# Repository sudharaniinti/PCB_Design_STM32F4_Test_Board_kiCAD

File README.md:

# STM32F4_based_PCB_Design_using_kiCAD
This repository contains all the files related to the design of a PCB using KICAD. The PCB is based on the STM32F4-based microcontroller and incorporates a USB interface and a Buck converter.

This repository includes the following files:

1. **Schematic (PDF File)**: A detailed PDF file that presents the circuit connections and component arrangement in a clear and concise manner.

2. **Schematic (kiCAD File)**: The original KICAD file of the schematic, allowing for easy editing and customization.

3. **Netlist**: The netlist file, an essential component of the design, which provides information about the electrical connections between various components and ensures accurate signal flow within the PCB.

4. **PCB Design**: The PCB layout file displaying the placement of components, routing traces, and layers used.

5. **Bill of Materials(BOM)**: The BOM file (in CSV format) listing all the components used in the design along with their quantities and specifications.

6. **Gerber Files**: These files (in ZIP format) are necessary for PCB fabrication. They include all the data required by the manufacturer to produce the physical PCB, such as copper layers, solder mask, silkscreen, drill holes, and board outline.

7. **Component Placement File**: This file (in CSV format) provides the precise coordinates and orientations for placing components on the PCB. It assists during the assembly process by ensuring accurate component placement.

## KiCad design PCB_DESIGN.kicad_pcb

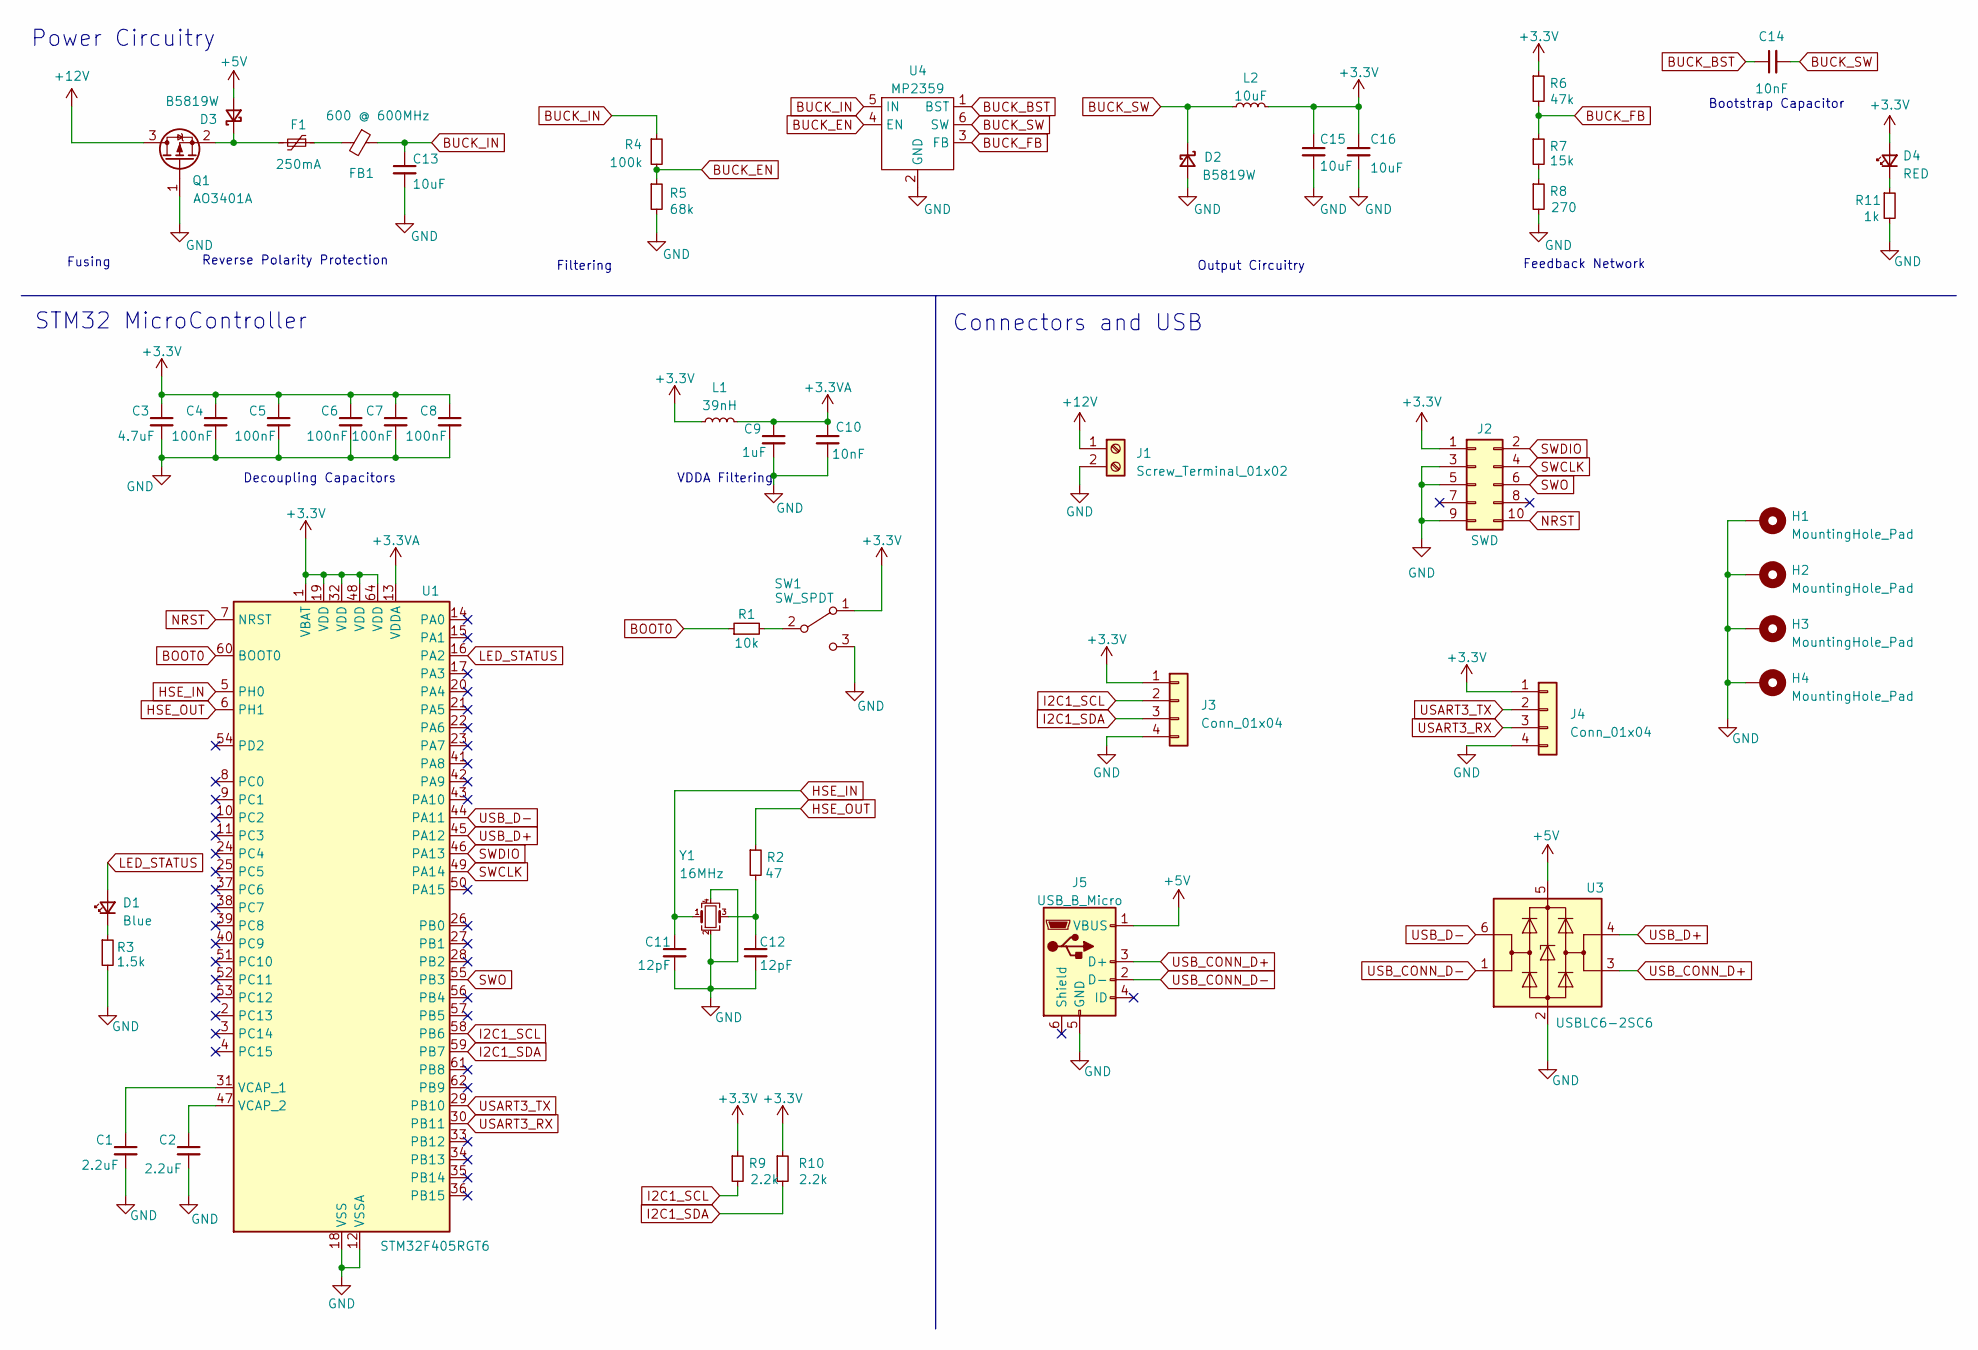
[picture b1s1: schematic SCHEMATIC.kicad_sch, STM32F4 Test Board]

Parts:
C1, C2: 2.2uF; C_0603_1608Metric
C3: 4.7uF; C_0603_1608Metric
C4, C5, C6, C7, C8: 100nF; C_0402_1005Metric
C9: 1uF; C_0402_1005Metric
C10: 10nF; C_0402_1005Metric
C11, C12: 12pF; C_0402_1005Metric
C13, C15, C16: 10uF; C_1206_3216Metric
C14: 10nF; C_0603_1608Metric
D1: Blue; LED_0603_1608Metric
D2, D3: B5819W; D_SOD-123
D4: RED; LED_0603_1608Metric
F1: 250mA; Fuse_1206_3216Metric
FB1: 600 @ 600MHz; L_0805_2012Metric
H1, H2, H3, H4: MountingHole_Pad; MountingHole_4.3mm_M4_Pad_Via
J1: Screw_Terminal_01x02; TerminalBlock_Phoenix_PT-1,5-2-3.5-H_1x02_P3.50mm_Horizontal
J2: SWD; PinHeader_2x05_P1.27mm_Vertical_SMD
J3, J4: Conn_01x04; Molex_PicoBlade_53048-0410_1x04_P1.25mm_Horizontal
J5: USB_B_Micro; USB_Micro-B_GCT_USB3076-30-A
L1: 39nH; L_0402_1005Metric
L2: 10uF; L_Sunlord_MWSA0518S
Q1: AO3401A; SOT-23
R1: 10k; R_0402_1005Metric
R2: 47; R_0402_1005Metric
R3: 1.5k; R_0603_1608Metric
R4: 100k; R_0603_1608Metric
R5: 68k; R_0603_1608Metric
R6: 47k; R_0603_1608Metric
R7: 15k; R_0603_1608Metric
R8: 270; R_0603_1608Metric
R9, R10: 2.2k; R_0402_1005Metric
R11: 1k; R_0603_1608Metric
SW1: SW_SPDT; SW_SPDT_PCM12
U1: STM32F405RGT6; LQFP-64_10x10mm_P0.5mm
U3: USBLC6-2SC6; SOT-23-6
U4: MP2359; SOT-23-6
Y1: 16MHz; Crystal_SMD_3225-4Pin_3.2x2.5mm

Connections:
+3.3V: C3.1, C4.1, C5.1, C6.1, C7.1, C8.1, C15.1, C16.1, D4.2 (A), J2.1, J3.1, J4.1, L1.1, L2.2, R6.1, R9.1, R10.1, SW1.1 (A), U1.1 (VBAT), U1.19 (VDD), U1.32 (VDD), U1.48 (VDD), U1.64 (VDD)
+3.3VA: C9.1, C10.1, L1.2, U1.13 (VDDA)
+5V: D3.2 (A), J5.1 (VBUS), U3.5 (VBUS)
+12V: J1.1, Q1.3 (D)
BOOT0: R1.1, U1.60 (BOOT0)
BUCK_BST: C14.1, U4.1 (BST)
BUCK_EN: R4.2, R5.1, U4.4 (EN)
BUCK_FB: R6.2, R7.1, U4.3 (FB)
BUCK_IN: C13.1, FB1.1, R4.1, U4.5 (IN)
BUCK_SW: C14.2, D2.1 (K), L2.1, U4.6 (SW)
GND: C1.2, C2.2, C3.2, C4.2, C5.2, C6.2, C7.2, C8.2, C9.2, C10.2, C11.2, C12.2, C13.2, C15.2, C16.2, D2.2 (A), H1.1, H2.1, H3.1, H4.1, J1.2, J2.3, J2.5, J2.9, J3.4, J4.4, J5.5 (GND), Q1.1 (G), R3.2, R5.2, R8.2, R11.2, SW1.3 (C), U1.12 (VSSA), U1.18 (VSS), U1.63 (VSS), U3.2 (GND), U4.2 (GND), Y1.2, Y1.4
HSE_IN: C11.1, U1.5 (PH0), Y1.1
HSE_OUT: R2.1, U1.6 (PH1)
I2C1_SCL: J3.2, R9.2, U1.58 (PB6)
I2C1_SDA: J3.3, R10.2, U1.59 (PB7)
LED_STATUS: D1.2 (A), U1.16 (PA2)
NRST: J2.10, U1.7 (NRST)
unnamed: C12.1, R2.2, Y1.3
unnamed: D1.1 (K), R3.1
unnamed: D3.1 (K), F1.2, Q1.2 (S)
unnamed: D4.1 (K), R11.1
unnamed: F1.1, FB1.2
unnamed: R7.2, R8.1
unnamed: R1.2, SW1.2 (B)
unnamed: C1.1, U1.31 (VCAP_1)
unnamed: C2.1, U1.47 (VCAP_2)
SWCLK: J2.4, U1.49 (PA14)
SWDIO: J2.2, U1.46 (PA13)
SWO: J2.6, U1.55 (PB3)
USART3_RX: J4.3, U1.30 (PB11)
USART3_TX: J4.2, U1.29 (PB10)
USB_CONN_D+: J5.3 (D+), U3.3 (I/O2)
USB_CONN_D-: J5.2 (D-), U3.1 (I/O1)
USB_D+: U1.45 (PA12), U3.4 (I/O2)
USB_D-: U1.44 (PA11), U3.6 (I/O1)

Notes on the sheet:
Decoupling Capacitors
Filtering
Fusing
Output Circuitry
Power Circuitry
VDDA Filtering
Feedback Network
Connectors and USB
STM32 MicroController
Reverse Polarity Protection
Bootstrap Capacitor

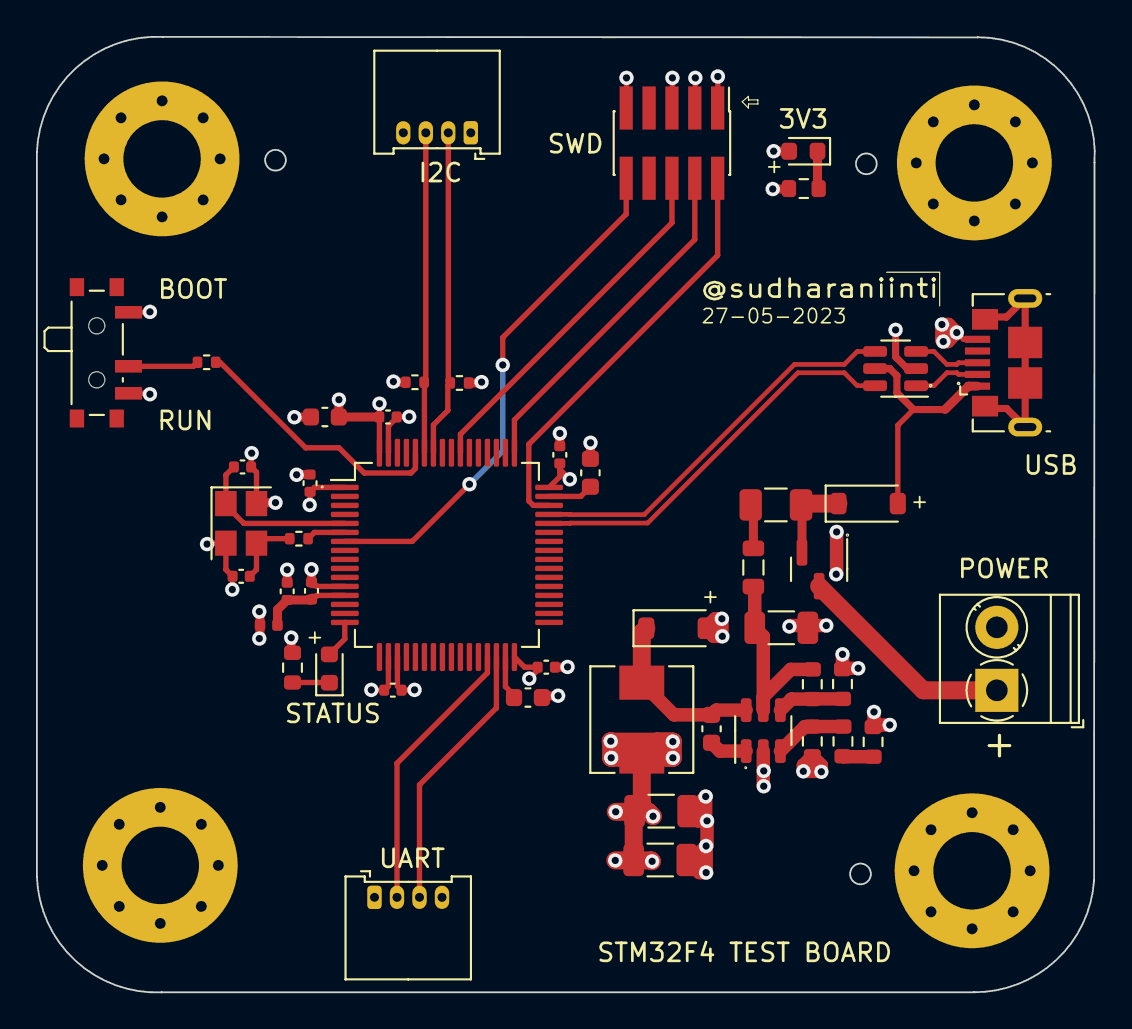
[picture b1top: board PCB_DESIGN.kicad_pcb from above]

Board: 4 copper layers, 58.8 x 53.1 mm, 50 parts (0 on the bottom side), 35 nets.

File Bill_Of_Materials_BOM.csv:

"Source:","E:\KiCAD_STM32\KiCAD_STM32.kicad_sch"
"Date:","5/28/2023 2:46:41 AM"
"Tool:","Eeschema 7.0.2"
"Generator:","C:\Program Files\KiCad\7.0\bin\scripting\plugins/bom_csv_grouped_by_value.py"
"Component Count:","50"

"Collated Components:"

"Item","Qty","Reference(s)","Value","LibPart","Footprint","Datasheet","DNP"
"1","2","C1, C2","2.2uF","Device:C_Small","Capacitor_SMD:C_0603_1608Metric","~",""
"2","1","C3","4.7uF","Device:C_Small","Capacitor_SMD:C_0603_1608Metric","~",""
"3","5","C4, C5, C6, C7, C8","100nF","Device:C_Small","Capacitor_SMD:C_0402_1005Metric","~",""
"4","1","C9","1uF","Device:C_Small","Capacitor_SMD:C_0402_1005Metric","~",""
"5","1","C10","10nF","Device:C_Small","Capacitor_SMD:C_0402_1005Metric","~",""
"6","2","C11, C12","12pF","Device:C_Small","Capacitor_SMD:C_0402_1005Metric","~",""
"7","3","C13, C15, C16","10uF","Device:C_Small","Capacitor_SMD:C_1206_3216Metric","~",""
"8","1","C14","10nF","Device:C_Small","Capacitor_SMD:C_0603_1608Metric","~",""
"9","1","D1","Blue","Device:LED_Small","LED_SMD:LED_0603_1608Metric","~",""
"10","2","D2, D3","B5819W","Device:D_Schottky_Small","Diode_SMD:D_SOD-123","~",""
"11","1","D4","RED","Device:LED_Small","LED_SMD:LED_0603_1608Metric","~",""
"12","1","F1","250mA","Device:Polyfuse_Small","Fuse:Fuse_1206_3216Metric","~",""
"13","1","FB1","600 @ 600MHz","Device:FerriteBead_Small","Inductor_SMD:L_0805_2012Metric","~",""
"14","4","H1, H2, H3, H4","MountingHole_Pad","Mechanical:MountingHole_Pad","MountingHole:MountingHole_4.3mm_M4_Pad_Via","~",""
"15","1","J1","Screw_Terminal_01x02","Connector:Screw_Terminal_01x02","TerminalBlock_Phoenix:TerminalBlock_Phoenix_PT-1,5-2-3.5-H_1x02_P3.50mm_Horizontal","~",""
"16","1","J2","SWD","Connector_Generic:Conn_02x05_Odd_Even","Connector_PinHeader_1.27mm:PinHeader_2x05_P1.27mm_Vertical_SMD","~",""
"17","2","J3, J4","Conn_01x04","Connector_Generic:Conn_01x04","Connector_Molex:Molex_PicoBlade_53048-0410_1x04_P1.25mm_Horizontal","~",""
"18","1","J5","USB_B_Micro","Connector:USB_B_Micro","Connector_USB:USB_Micro-B_GCT_USB3076-30-A","~",""
"19","1","L1","39nH","Device:L_Small","Inductor_SMD:L_0402_1005Metric","~",""
"20","1","L2","10uF","Device:L_Small","Inductor_SMD:L_Sunlord_MWSA0518S","~",""
"21","1","Q1","AO3401A","Transistor_FET:AO3401A","Package_TO_SOT_SMD:SOT-23","http://www.aosmd.com/pdfs/datasheet/AO3401A.pdf",""
"22","1","R1","10k","Device:R_Small","Resistor_SMD:R_0402_1005Metric","~",""
"23","1","R2","47","Device:R_Small","Resistor_SMD:R_0402_1005Metric","~",""
"24","1","R3","1.5k","Device:R_Small","Resistor_SMD:R_0603_1608Metric","~",""
"25","1","R4","100k","Device:R_Small","Resistor_SMD:R_0603_1608Metric","~",""
"26","1","R5","68k","Device:R_Small","Resistor_SMD:R_0603_1608Metric","~",""
"27","1","R6","47k","Device:R_Small","Resistor_SMD:R_0603_1608Metric","~",""
"28","1","R7","15k","Device:R_Small","Resistor_SMD:R_0603_1608Metric","~",""
"29","1","R8","270","Device:R_Small","Resistor_SMD:R_0603_1608Metric","~",""
"30","2","R9, R10","2.2k","Device:R_Small","Resistor_SMD:R_0402_1005Metric","~",""
"31","1","R11","1k","Device:R_Small","Resistor_SMD:R_0603_1608Metric","~",""
"32","1","SW1","SW_SPDT","Switch:SW_SPDT","Button_Switch_SMD:SW_SPDT_PCM12","~",""
"33","1","U1","STM32F405RGT6","MCU_ST_STM32F4:STM32F405RGTx","Package_QFP:LQFP-64_10x10mm_P0.5mm","https://www.st.com/resource/en/datasheet/stm32f405rg.pdf",""
"34","1","U3","USBLC6-2SC6","Power_Protection:USBLC6-2SC6","Package_TO_SOT_SMD:SOT-23-6","https://www.st.com/resource/en/datasheet/usblc6-2.pdf",""
"35","1","U4","MP2359",":MP2359_1","Package_TO_SOT_SMD:SOT-23-6","",""
"36","1","Y1","16MHz","Device:Crystal_GND24_Small","Crystal:Crystal_SMD_3225-4Pin_3.2x2.5mm","~",""
